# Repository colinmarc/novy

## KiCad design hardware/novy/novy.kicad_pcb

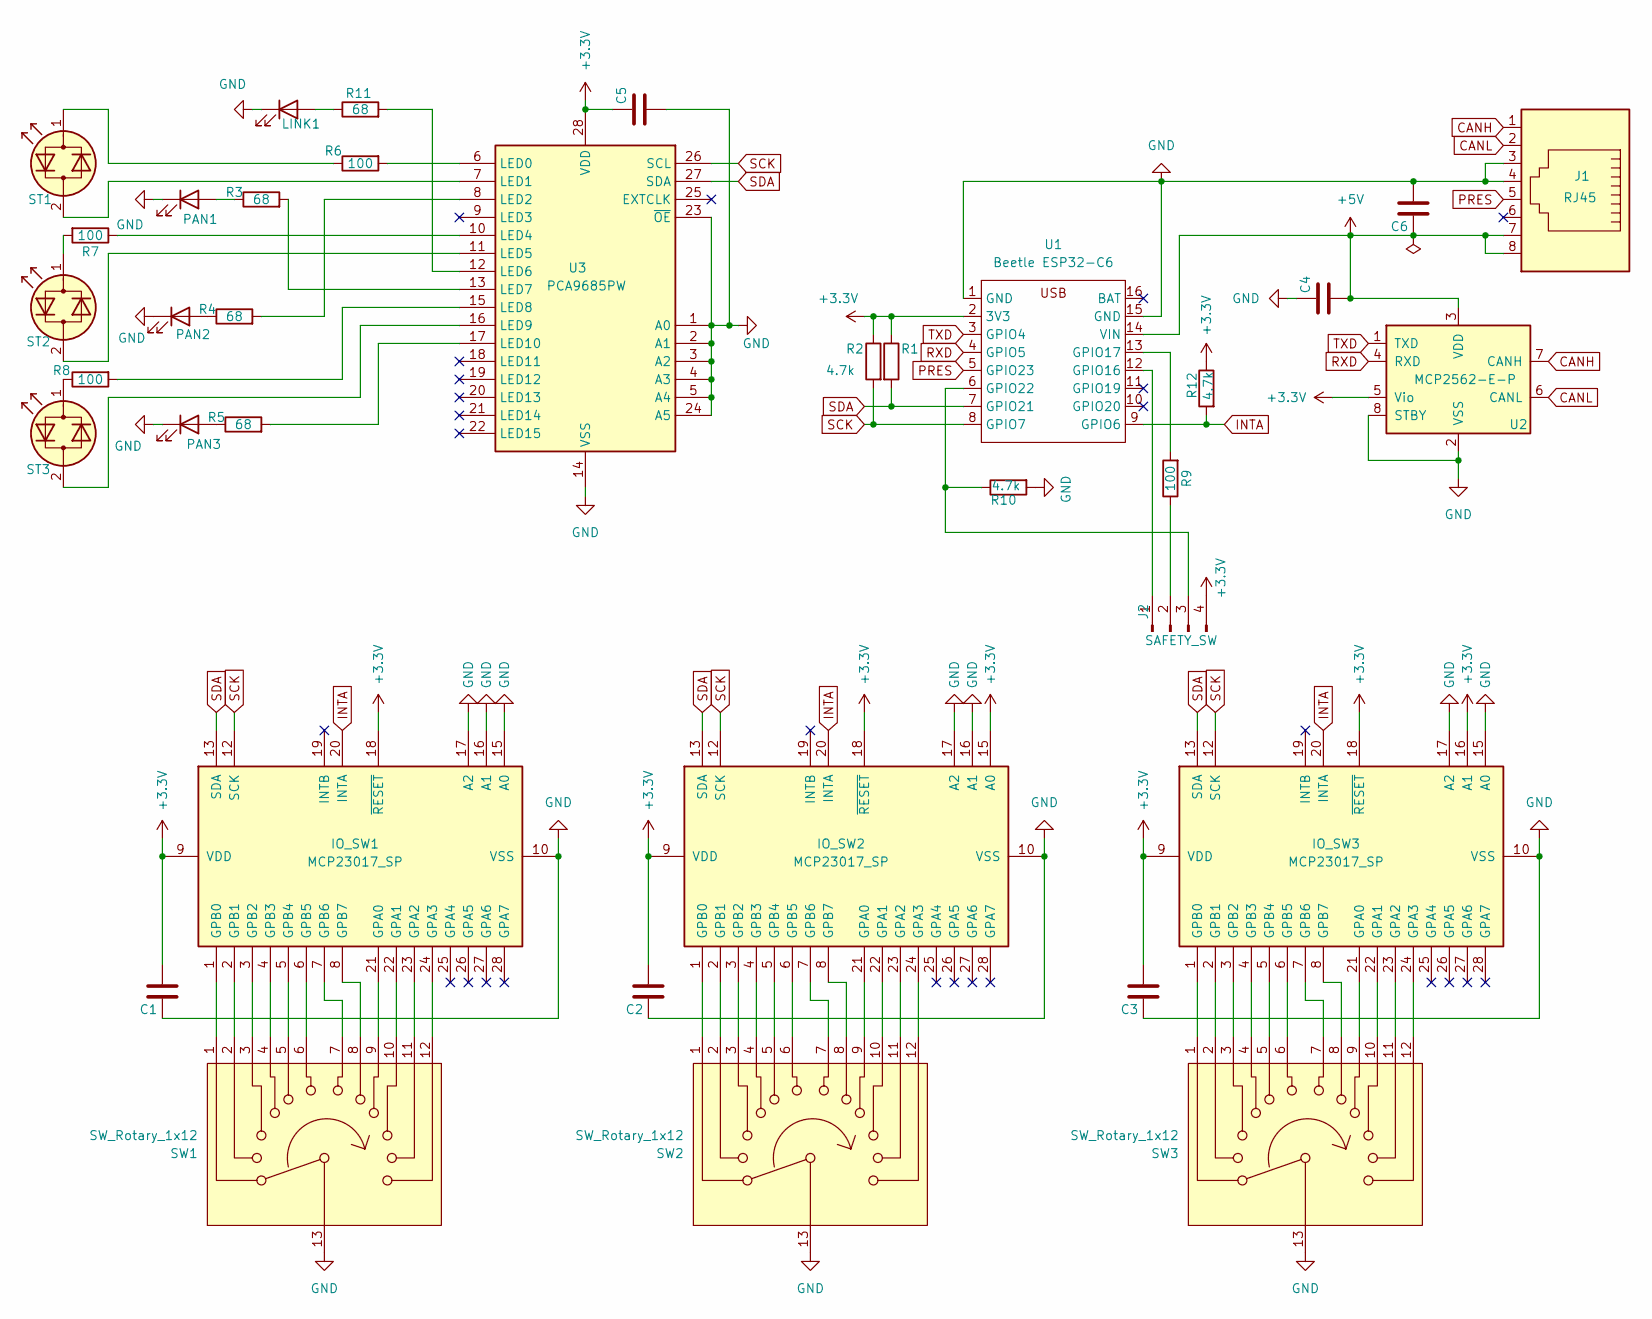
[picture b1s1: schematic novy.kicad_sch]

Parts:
C1, C2, C3, C4, C5: C; C_Rect_L7.0mm_W2.0mm_P5.00mm
C6: 10uF; C_Rect_L7.0mm_W2.0mm_P5.00mm
IO_SW1, IO_SW2, IO_SW3: MCP23017_SP; DIP-28_W7.62mm
J1: RJ45; RJ45_Amphenol_54602-x08_Horizontal
J2: SAFETY_SW; PinHeader_1x04_P2.54mm_Vertical
LINK1: LED_D3.0mm
PAN1: LED_D3.0mm
PAN2: PAN2; LED_D3.0mm
PAN3: PAN3; LED_D3.0mm
R1, R2, R10, R12: 4.7k; R_0603_1608Metric_Pad0.98x0.95mm_HandSolder
R3, R4, R5, R11: 68; R_0603_1608Metric_Pad0.98x0.95mm_HandSolder
R6, R7, R8, R9: 100; R_0603_1608Metric_Pad0.98x0.95mm_HandSolder
ST1, ST2, ST3: LED_Dual_Bidirectional; LED_D3.0mm
SW1, SW2, SW3: SW_Rotary_1x12; Elma_04-1124-20
U1: Beetle ESP32-C6; esp32-c6-beetle
U2: MCP2562-E-P; DIP-8_W7.62mm
U3: PCA9685PW; TSSOP-28_4.4x9.7mm_P0.65mm

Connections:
+5V: C4.1, C6.2, J1.7, J1.8, U1.14 (VIN), U2.3 (VDD)
CANH: J1.1, U2.7 (CANH); also elsewhere on the board
CANL: J1.2, U2.6 (CANL); also elsewhere on the board
GND: C1.2, C2.2, C3.2, C4.2, C5.1, C6.1, IO_SW1.10 (VSS), IO_SW1.15 (A0), IO_SW1.16 (A1), IO_SW1.17 (A2), IO_SW2.10 (VSS), IO_SW2.16 (A1), IO_SW2.17 (A2), IO_SW3.10 (VSS), IO_SW3.15 (A0), IO_SW3.17 (A2), J1.3, J1.4, LINK1.1 (K), PAN1.1 (K), PAN2.1 (K), PAN3.1 (K), R10.2, SW1.13, SW2.13, SW3.13, U1.1 (GND), U1.15 (GND), U2.2 (VSS), U2.8 (STBY), U3.1 (A0), U3.2 (A1), U3.3 (A2), U3.4 (A3), U3.5 (A4), U3.14 (VSS), U3.23 (~OE), U3.24 (A5)
INTA: IO_SW1.20 (INTA), IO_SW2.20 (INTA), IO_SW3.20 (INTA), R12.2, U1.9 (GPIO6)
unnamed: IO_SW1.21 (GPA0), SW1.9
unnamed: IO_SW1.22 (GPA1), SW1.10
unnamed: IO_SW1.23 (GPA2), SW1.11
unnamed: IO_SW1.24 (GPA3), SW1.12
unnamed: IO_SW1.1 (GPB0), SW1.1
unnamed: IO_SW1.2 (GPB1), SW1.2
unnamed: IO_SW1.3 (GPB2), SW1.3
unnamed: IO_SW1.4 (GPB3), SW1.4
unnamed: IO_SW1.5 (GPB4), SW1.5
unnamed: IO_SW1.6 (GPB5), SW1.6
unnamed: IO_SW1.7 (GPB6), SW1.7
unnamed: IO_SW1.8 (GPB7), SW1.8
unnamed: IO_SW2.21 (GPA0), SW2.9
unnamed: IO_SW2.22 (GPA1), SW2.10
unnamed: IO_SW2.23 (GPA2), SW2.11
unnamed: IO_SW2.24 (GPA3), SW2.12
unnamed: IO_SW2.1 (GPB0), SW2.1
unnamed: IO_SW2.2 (GPB1), SW2.2
unnamed: IO_SW2.3 (GPB2), SW2.3
unnamed: IO_SW2.4 (GPB3), SW2.4
unnamed: IO_SW2.5 (GPB4), SW2.5
unnamed: IO_SW2.6 (GPB5), SW2.6
unnamed: IO_SW2.7 (GPB6), SW2.7
unnamed: IO_SW2.8 (GPB7), SW2.8
unnamed: IO_SW3.21 (GPA0), SW3.9
unnamed: IO_SW3.22 (GPA1), SW3.10
unnamed: IO_SW3.23 (GPA2), SW3.11
unnamed: IO_SW3.24 (GPA3), SW3.12
unnamed: IO_SW3.1 (GPB0), SW3.1
unnamed: IO_SW3.2 (GPB1), SW3.2
unnamed: IO_SW3.3 (GPB2), SW3.3
unnamed: IO_SW3.4 (GPB3), SW3.4
unnamed: IO_SW3.5 (GPB4), SW3.5
unnamed: IO_SW3.6 (GPB5), SW3.6
unnamed: IO_SW3.7 (GPB6), SW3.7
unnamed: IO_SW3.8 (GPB7), SW3.8
unnamed: J2.1, U1.12 (GPIO16)
unnamed: J2.2, R9.1
unnamed: J2.3, R10.1, U1.6 (GPIO22)
unnamed: LINK1.2 (A), R11.1
unnamed: PAN1.2 (A), R3.1
unnamed: PAN2.2 (A), R4.1
unnamed: PAN3.2 (A), R5.1
unnamed: ST1.2 (AK), U3.7 (LED1)
unnamed: R6.1, ST1.1 (KA)
unnamed: ST2.2 (AK), U3.11 (LED5)
unnamed: R7.2, ST2.1 (KA)
unnamed: ST3.2 (AK), U3.16 (LED9)
unnamed: R8.1, ST3.1 (KA)
unnamed: R9.2, U1.13 (GPIO17)
unnamed: R6.2, U3.6 (LED0)
unnamed: R4.2, U3.8 (LED2)
unnamed: R7.1, U3.10 (LED4)
unnamed: R11.2, U3.12 (LED6)
unnamed: R3.2, U3.13 (LED7)
unnamed: R8.2, U3.15 (LED8)
unnamed: R5.2, U3.17 (LED10)
RXD: U1.4 (GPIO5), U2.4 (RXD)
SCK: IO_SW1.12 (SCK), IO_SW2.12 (SCK), IO_SW3.12 (SCK), R2.2, U1.8 (GPIO7), U3.26 (SCL)
SDA: IO_SW1.13 (SDA), IO_SW2.13 (SDA), IO_SW3.13 (SDA), R1.2, U1.7 (GPIO21), U3.27 (SDA)
TXD: U1.3 (GPIO4), U2.1 (TXD)

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
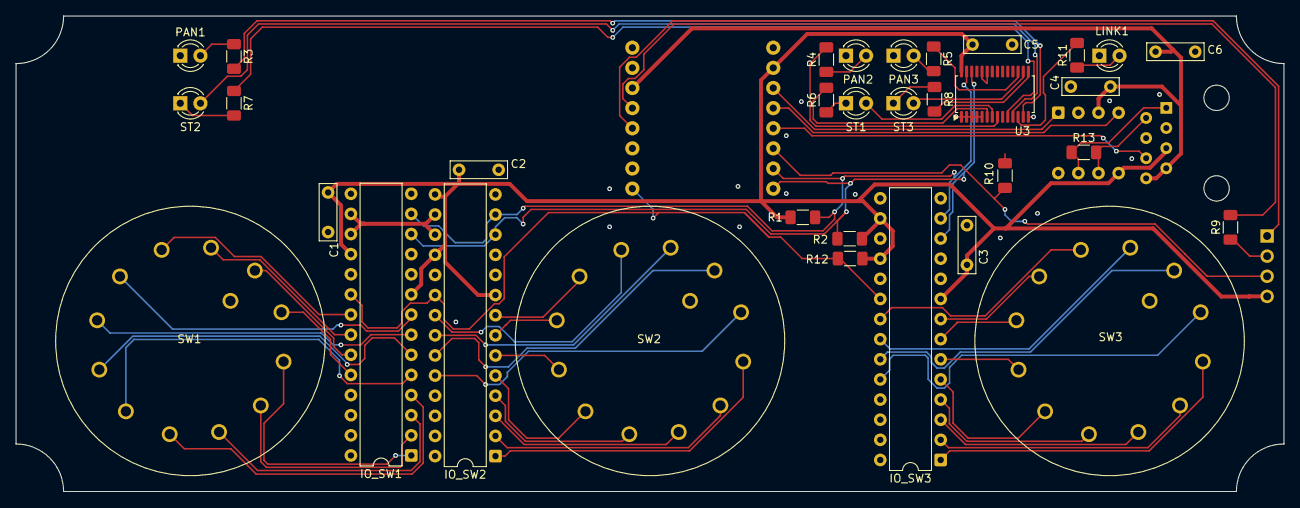
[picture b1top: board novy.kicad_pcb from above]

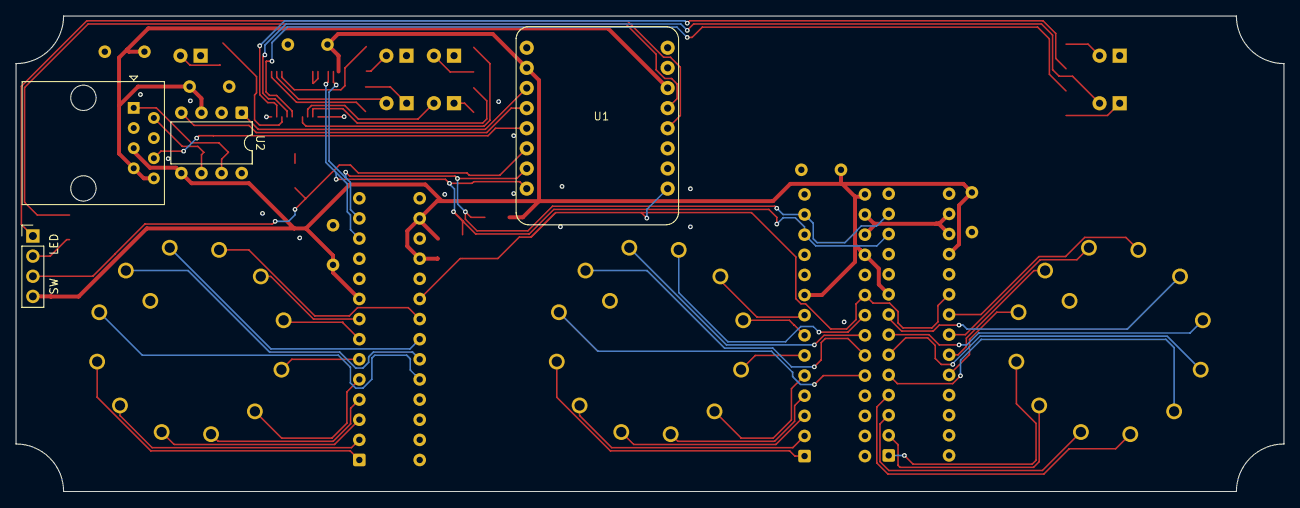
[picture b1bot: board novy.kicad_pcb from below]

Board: 2 copper layers, 160.0 x 60.0 mm, 37 parts (4 on the bottom side), 68 nets.

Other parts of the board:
R13: 120; R_1206_3216Metric_Pad1.30x1.75mm_HandSolder

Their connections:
CANH: R13.1; also elsewhere on the board
CANL: R13.2; also elsewhere on the board

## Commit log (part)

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2026-05-25 working prototype
